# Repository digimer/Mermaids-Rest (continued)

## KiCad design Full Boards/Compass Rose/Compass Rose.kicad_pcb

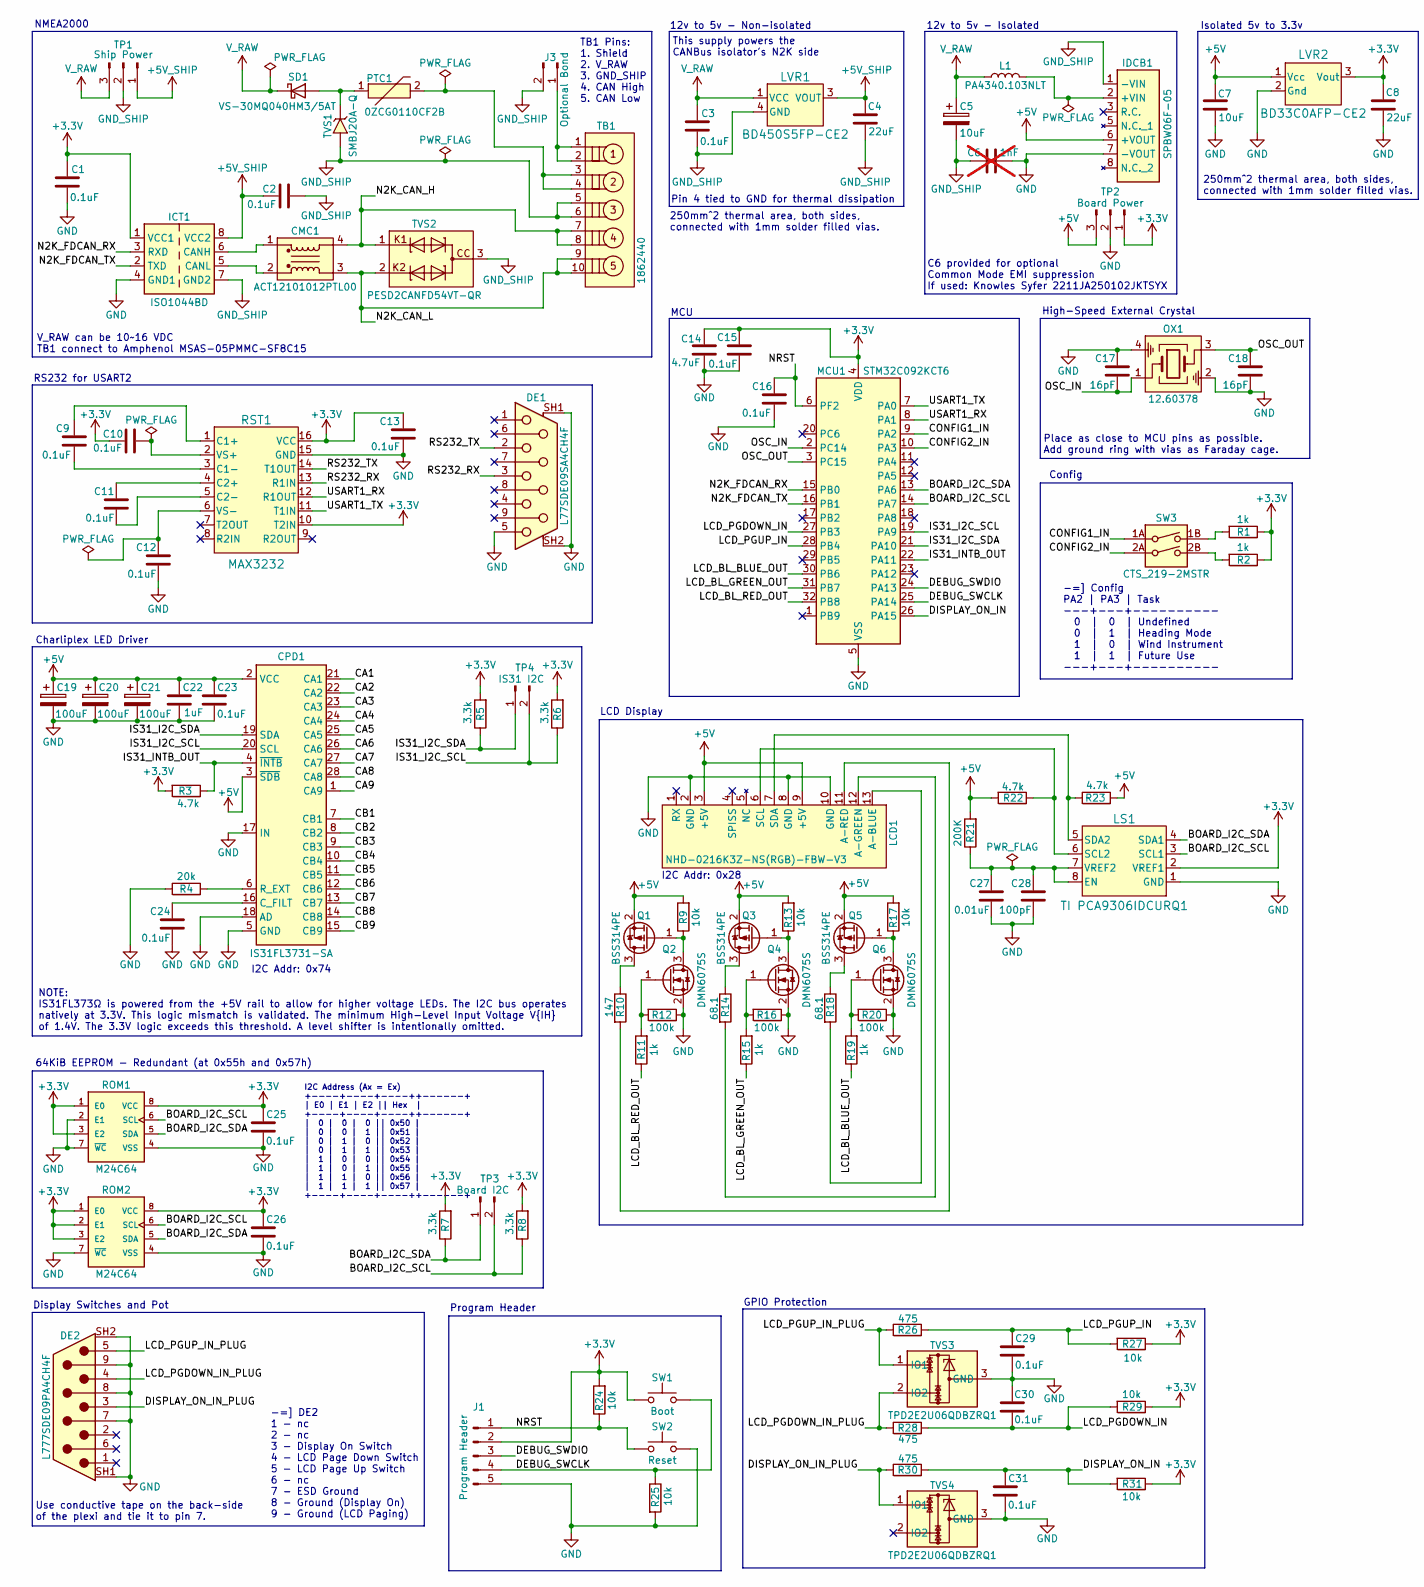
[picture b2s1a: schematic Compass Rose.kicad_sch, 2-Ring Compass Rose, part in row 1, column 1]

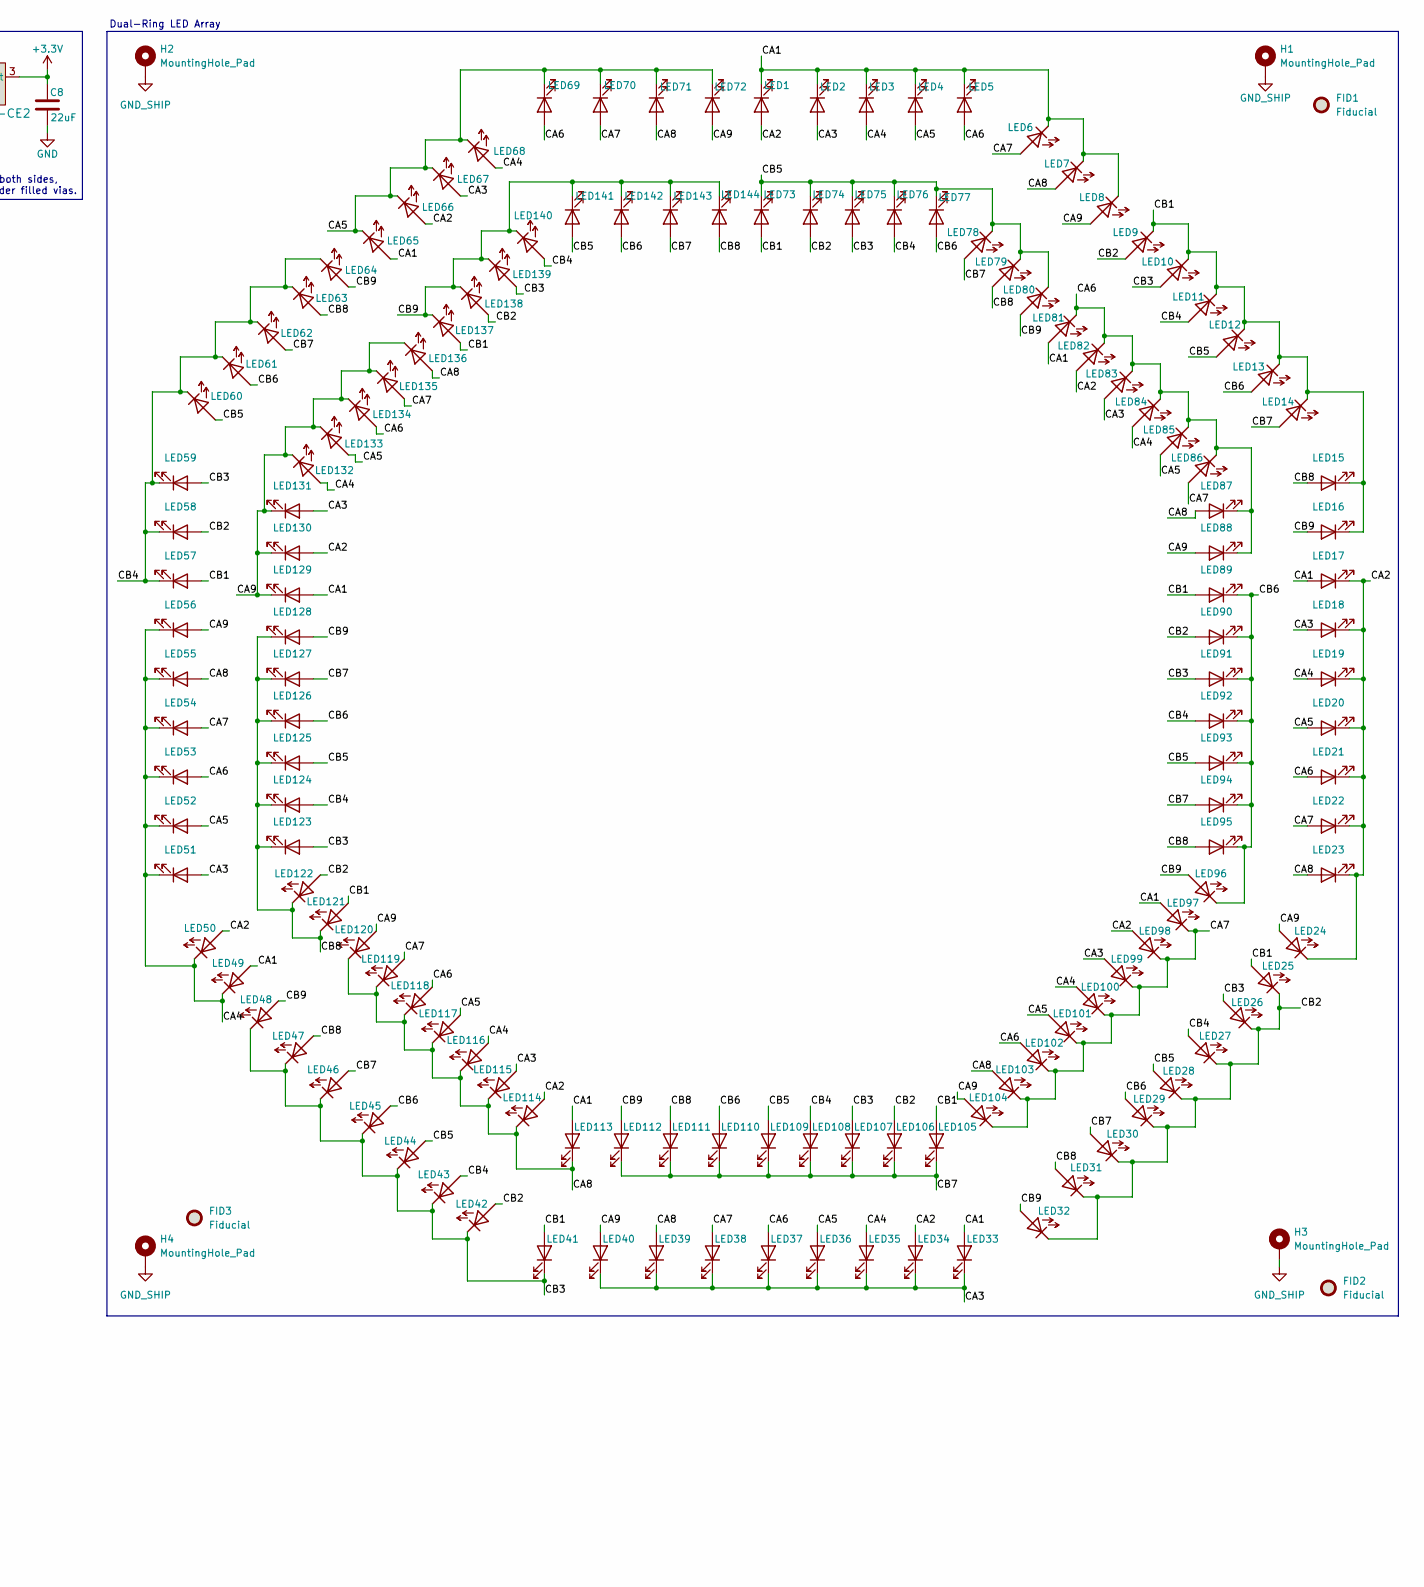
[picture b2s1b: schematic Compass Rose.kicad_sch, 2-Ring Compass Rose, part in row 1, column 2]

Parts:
C1, C2, C3, C9, C10, C11, C12, C13, C15, C16, C23, C24, C25, C26, C29, C30, C31: 0.1uF; Kyocera AVX 0805; Part Kyocera 08051C104K4Z2A
C4, C8: 22uF; Murata GCJ31CR71A; Part Murata GCJ31CR71A226KE01L
C5: 10uF; Kyocera AVX 1206; Part Kyocera 12105C106K4Z2A
C6: 1nF; Knowles Syfer 2211JA25; not fitted
C7: 10uF; TDK CGA5; Part TDK CGA5L1X7R1E106K160DC
C14: 4.7uF; Kyocera AVX 1206; Part Kyocera 12065C475K4Z2A
C17, C18: 16pF; Kemet C0603X; Part Kemet C0603X160J5GACAUTO
C19, C20, C21: 100uF; CP_Radial_D8.0mm_P3.50mm; Part Kemet A7C0KS107M1HAAS031
C22: 1uF; Kemet C1206C; Part Kemet C1206X105J1RACAUTO
C27: 0.01uF; Kemet C0805X; Part Kemet FA18NP01H103JNU06
C28: 100pF; Kemet C0805X; Part Kemet C0805X101J5GACAUTO
CMC1: ACT12101012PTL00; TDK ACT12101012PTL00; Part TDK ACT12101012PTL00
CPD1: IS31FL3731-SA; SSOP-28_5.3x10.2mm_P0.65mm; Part Lumissil IS31FL3731-SALS2-TR
DE1: L77SDE09SA4CH4F; Amphenol_L77SDE09SA4CH4F; Part Amphenol L77SDE09SA4CH4F
DE2: L777SDE09PA4CH4F; Amphenol L777SDE09PA4CH4F; Part AAmphenol L777SDE09PA4CH4F
FID1, FID2, FID3: Fiducial; Fiducial_0.5mm_Mask1.5mm
H1, H2, H3, H4: MountingHole_Pad; MountingHole_4mm_Pad_Via
ICT1: ISO1044BD; TI ISO1044BDR; Part TI ISO1044BDR
IDCB1: SPBW06F-05; Meanwell SPBW06F05; Part Meanwell SPBW06F-05
J1: Program Header; PinHeader_1x05_P2.54mm_Horizontal
J3: Optional Bond; PinHeader_1x02_P2.54mm_Vertical
L1: PA4340.103NLT; Pulse PA4340.103NLT; Part Pulse PA4340.103NLT
LCD1: NHD-0216K3Z-NS(RGB)-FBW-V3; Newhaven Display NHD-0216K3Z-NS(RGB)-FBW-V3; Part Newhaven Display NHD-0216K3Z-NS(RGB)-FB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
LED1, LED2, LED3, LED4, LED5, LED6, LED7, LED8, LED9, LED10, LED11, LED12, LED13, LED14, LED15, LED16, LED17, LED18, LED19, LED20, LED21, LED22, LED23, LED24, LED25, LED26, LED27, LED28, LED29, LED30, LED31, LED32, LED33, LED34, LED35, LED36, LED37, LED38, LED39, LED40, LED41, LED42, LED43, LED44, LED45, LED46, LED47, LED48, LED49, LED50, LED51, LED52, LED53, LED54, LED55, LED56, LED57, LED58, LED59, LED60, LED61, LED62, LED63, LED64, LED65, LED66, LED67, LED68, LED69, LED70, LED71, LED72, LED73, LED74, LED75, LED76, LED77, LED78, LED79, LED80, LED81, LED82, LED83, LED84, LED85, LED86, LED87, LED88, LED89, LED90, LED91, LED92, LED93, LED94, LED95, LED96, LED97, LED98, LED99, LED100, LED101, LED102, LED103, LED104, LED105, LED106, LED107, LED108, LED109, LED110, LED111, LED112, LED113, LED114, LED115, LED116, LED117, LED118, LED119, LED120, LED121, LED122, LED123, LED124, LED125, LED126, LED127, LED128, LED129, LED130, LED131, LED132, LED133, LED134, LED135, LED136, LED137, LED138, LED139, LED140, LED141, LED142, LED143, LED144: WP383SURDTK; Kingbright WP383SURDTK; Part Kingbright WP383SURDTK
LS1: TI PCA9306IDCURQ1; TI PCA9306; Part Texas Instruments PCA9306IDCURQ1
LVR1: BD450S5FP-CE2; Rohm BD4xxS5 TO252-3; Part Rohm BD450S5FP-CE2
LVR2: BD33C0AFP-CE2; Rohm BD33C0; Part Rohm BD33C0AFP-CE2
MCU1: STM32C092KCT6; STM STM32C0 LQFP-32; Part STM STM32C092KCT6
OX1: 12.60378; Crystal_SMD_3225-4Pin_3.2x2.5mm; Part Geyer 12.60378
PTC1: 0ZCG0110CF2B; Bel Fuse 0ZCG; Part Bel Fuse 0ZCG0110CF2B
Q1, Q3, Q5: BSS314PE; SOT-23; Part Infineon BSS314PEH6327XTSA1
Q2, Q4, Q6: DMN6075S; SOT-23; Part Diodes Inc DMN6075SQ-7
R1, R2, R11, R15, R19: 1k; Stackpole RNCP0805; Part Stackpole RNCP0805FTD1K00
R3, R22, R23: 4.7k; Stackpole RMCA0805; Part Stackpole RMCA0805FT4K70-HP
R4: 20k; Stackpole RMCA0805; Part Stackpole RMCA0805FT20K0-HP
R5, R6, R7, R8: 3.3k; Stackpole RNCF0805; Part Stackpole RNCF0805DTE3K30
R9, R13, R17, R24, R25, R27, R29, R31: 10k; Stackpole RMCA0805; Part Stackpole RMCA0805FT10K0-HP
R10: 147; Stackpole RNCP0805; Part Stackpole RNCP0805FTD150R
R12, R16, R20: 100k; Stackpole RMCA0805; Part Stackpole RMCA0805FT100K-HP
R14, R18: 68.1; Stackpole RNCP0805; Part Stackpole RNCP0805FTD68R1
R21: 200K; Yageo AE0805; Part Yageo RNCP0805FTD475R
R26, R28, R30: 475; Stackpole RNCP0805; Part Stackpole RNCP0805FTD475R
ROM1, ROM2: M24C64; STM M24C64-RMN6P; Part STM M24C64-RMN6P
RST1: MAX3232; TI MAX3232EIPWRQ1; Part TI MAX3232EIPWRQ1
SD1: VS-30MQ040HM3/5AT; D_SMA; Part Vishay VS-30MQ040HM3/5AT
SW1: Boot; Same Sky TS03-66; Part Same Sky TS03-66-50-BK-160-LCR-D-67
SW2: Reset; Same Sky TS03-66; Part Same Sky TS03-66-50-BK-160-LCR-D-67
SW3: CTS_219-2MSTR; CTS 219-2MSTR; Part CTS 219-2MSTR
TB1: 1862440; Phoenix Contact 1862440; Part Phoenix Contact 1862440
TP1: Ship Power; PinHeader_1x03_P2.54mm_Vertical
TP2: Board Power; PinHeader_1x03_P2.54mm_Vertical
TP3: Board I2C; PinHeader_1x02_P2.54mm_Vertical
TP4: IS31 I2C; PinHeader_1x02_P2.54mm_Vertical
TVS1: SMBJ20A-Q; Bourns SMBJ20; Part Bourns SMBJ20A-Q
TVS2: PESD2CANFD54VT-QR; Nexperia PESD2CANFD; Part Nexperia PESD2CANFD54VT-QR
TVS3, TVS4: TPD2E2U06QDBZRQ1; TI TPD2E2U06; Part TI TPD2E2U06QDBZRQ1

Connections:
+3.3V: C1.2, C8.2, C10.2, C13.2, C14.1, C15.2, C25.2, C26.2, ICT1.1 (VCC1), J1.2, LS1.2 (VREF1), LVR2.3 (Vout), MCU1.4 (VDD), R1.1, R2.1, R3.2, R5.2, R6.2, R7.2, R8.2, R24.2, R27.1, R29.1, R31.1, ROM1.1 (E0), ROM1.3 (E2), ROM1.8 (VCC), ROM2.1 (E0), ROM2.2 (E1), ROM2.3 (E2), ROM2.8 (VCC), RST1.10 (T2IN), RST1.16 (VCC), SW1.1 (A), SW1.2 (A), TP2.1
+5V: C7.2, C19.1, C20.1, C21.1, C22.1, C23.2, CPD1.2 (VCC), CPD1.3 (~SDB), IDCB1.6 (+VOUT), LCD1.3 (+5V), LCD1.9 (+5V), LVR2.1 (Vcc), Q1.2 (S), Q3.2 (S), Q5.2 (S), R9.2, R13.2, R17.2, R21.2, R22.2, R23.2, TP2.3
+5V_SHIP: C2.2, C4.2, ICT1.8 (VCC2), LVR1.3 (VOUT), TP1.1
/BOARD_I2C_SCL: LS1.3 (SCL1), MCU1.14 (PA7), R8.1, ROM1.6 (SCL), ROM2.6 (SCL), TP3.2
/BOARD_I2C_SDA: LS1.4 (SDA1), MCU1.13 (PA6), R7.1, ROM1.5 (SDA), ROM2.5 (SDA), TP3.1
/CA1: CPD1.21 (CA1), LED1.1 (K), LED2.1 (K), LED3.1 (K), LED4.1 (K), LED5.1 (K), LED6.1 (K), LED7.1 (K), LED8.1 (K), LED17.2 (A), LED33.2 (A), LED49.2 (A), LED65.2 (A), LED81.2 (A), LED97.2 (A), LED113.2 (A), LED129.2 (A)
/CA2: CPD1.22 (CA2), LED1.2 (A), LED17.1 (K), LED18.1 (K), LED19.1 (K), LED20.1 (K), LED21.1 (K), LED22.1 (K), LED23.1 (K), LED24.1 (K), LED34.2 (A), LED50.2 (A), LED66.2 (A), LED82.2 (A), LED98.2 (A), LED114.2 (A), LED130.2 (A)
/CA3: CPD1.23 (CA3), LED2.2 (A), LED18.2 (A), LED33.1 (K), LED34.1 (K), LED35.1 (K), LED36.1 (K), LED37.1 (K), LED38.1 (K), LED39.1 (K), LED40.1 (K), LED51.2 (A), LED67.2 (A), LED83.2 (A), LED99.2 (A), LED115.2 (A), LED131.2 (A)
/CA4: CPD1.24 (CA4), LED3.2 (A), LED19.2 (A), LED35.2 (A), LED49.1 (K), LED50.1 (K), LED51.1 (K), LED52.1 (K), LED53.1 (K), LED54.1 (K), LED55.1 (K), LED56.1 (K), LED68.2 (A), LED84.2 (A), LED100.2 (A), LED116.2 (A), LED132.2 (A)
/CA5: CPD1.25 (CA5), LED4.2 (A), LED20.2 (A), LED36.2 (A), LED52.2 (A), LED65.1 (K), LED66.1 (K), LED67.1 (K), LED68.1 (K), LED69.1 (K), LED70.1 (K), LED71.1 (K), LED72.1 (K), LED85.2 (A), LED101.2 (A), LED117.2 (A), LED133.2 (A)
/CA6: CPD1.26 (CA6), LED5.2 (A), LED21.2 (A), LED37.2 (A), LED53.2 (A), LED69.2 (A), LED81.1 (K), LED82.1 (K), LED83.1 (K), LED84.1 (K), LED85.1 (K), LED86.1 (K), LED87.1 (K), LED88.1 (K), LED102.2 (A), LED118.2 (A), LED134.2 (A)
/CA7: CPD1.27 (CA7), LED6.2 (A), LED22.2 (A), LED38.2 (A), LED54.2 (A), LED70.2 (A), LED86.2 (A), LED97.1 (K), LED98.1 (K), LED99.1 (K), LED100.1 (K), LED101.1 (K), LED102.1 (K), LED103.1 (K), LED104.1 (K), LED119.2 (A), LED135.2 (A)
/CA8: CPD1.28 (CA8), LED7.2 (A), LED23.2 (A), LED39.2 (A), LED55.2 (A), LED71.2 (A), LED87.2 (A), LED103.2 (A), LED113.1 (K), LED114.1 (K), LED115.1 (K), LED116.1 (K), LED117.1 (K), LED118.1 (K), LED119.1 (K), LED120.1 (K), LED136.2 (A)
/CA9: CPD1.1 (CA9), LED8.2 (A), LED24.2 (A), LED40.2 (A), LED56.2 (A), LED72.2 (A), LED88.2 (A), LED104.2 (A), LED120.2 (A), LED129.1 (K), LED130.1 (K), LED131.1 (K), LED132.1 (K), LED133.1 (K), LED134.1 (K), LED135.1 (K), LED136.1 (K)
/CB1: CPD1.7 (CB1), LED9.1 (K), LED10.1 (K), LED11.1 (K), LED12.1 (K), LED13.1 (K), LED14.1 (K), LED15.1 (K), LED16.1 (K), LED25.2 (A), LED41.2 (A), LED57.2 (A), LED73.2 (A), LED89.2 (A), LED105.2 (A), LED121.2 (A), LED137.2 (A)
/CB2: CPD1.8 (CB2), LED9.2 (A), LED25.1 (K), LED26.1 (K), LED27.1 (K), LED28.1 (K), LED29.1 (K), LED30.1 (K), LED31.1 (K), LED32.1 (K), LED42.2 (A), LED58.2 (A), LED74.2 (A), LED90.2 (A), LED106.2 (A), LED122.2 (A), LED138.2 (A)
/CB3: CPD1.9 (CB3), LED10.2 (A), LED26.2 (A), LED41.1 (K), LED42.1 (K), LED43.1 (K), LED44.1 (K), LED45.1 (K), LED46.1 (K), LED47.1 (K), LED48.1 (K), LED59.2 (A), LED75.2 (A), LED91.2 (A), LED107.2 (A), LED123.2 (A), LED139.2 (A)
/CB4: CPD1.10 (CB4), LED11.2 (A), LED27.2 (A), LED43.2 (A), LED57.1 (K), LED58.1 (K), LED59.1 (K), LED60.1 (K), LED61.1 (K), LED62.1 (K), LED63.1 (K), LED64.1 (K), LED76.2 (A), LED92.2 (A), LED108.2 (A), LED124.2 (A), LED140.2 (A)
/CB5: CPD1.11 (CB5), LED12.2 (A), LED28.2 (A), LED44.2 (A), LED60.2 (A), LED73.1 (K), LED74.1 (K), LED75.1 (K), LED76.1 (K), LED77.1 (K), LED78.1 (K), LED79.1 (K), LED80.1 (K), LED93.2 (A), LED109.2 (A), LED125.2 (A), LED141.2 (A)
/CB6: CPD1.12 (CB6), LED13.2 (A), LED29.2 (A), LED45.2 (A), LED61.2 (A), LED77.2 (A), LED89.1 (K), LED90.1 (K), LED91.1 (K), LED92.1 (K), LED93.1 (K), LED94.1 (K), LED95.1 (K), LED96.1 (K), LED110.2 (A), LED126.2 (A), LED142.2 (A)
/CB7: CPD1.13 (CB7), LED14.2 (A), LED30.2 (A), LED46.2 (A), LED62.2 (A), LED78.2 (A), LED94.2 (A), LED105.1 (K), LED106.1 (K), LED107.1 (K), LED108.1 (K), LED109.1 (K), LED110.1 (K), LED111.1 (K), LED112.1 (K), LED127.2 (A), LED143.2 (A)
/CB8: CPD1.14 (CB8), LED15.2 (A), LED31.2 (A), LED47.2 (A), LED63.2 (A), LED79.2 (A), LED95.2 (A), LED111.2 (A), LED121.1 (K), LED122.1 (K), LED123.1 (K), LED124.1 (K), LED125.1 (K), LED126.1 (K), LED127.1 (K), LED128.1 (K), LED144.2 (A)
/CB9: CPD1.15 (CB9), LED16.2 (A), LED32.2 (A), LED48.2 (A), LED64.2 (A), LED80.2 (A), LED96.2 (A), LED112.2 (A), LED128.2 (A), LED137.1 (K), LED138.1 (K), LED139.1 (K), LED140.1 (K), LED141.1 (K), LED142.1 (K), LED143.1 (K), LED144.1 (K)
/CONFIG1_IN: MCU1.9 (PA2), SW3.1A
/CONFIG2_IN: MCU1.10 (PA3), SW3.2A
/DEBUG_SWCLK: J1.4, MCU1.25 (PA14), R25.1, SW1.3 (B), SW1.4 (B)
/DEBUG_SWDIO: J1.3, MCU1.24 (PA13)
/DISPLAY_ON_IN: C31.2, MCU1.26 (PA15), R30.2, R31.2
/DISPLAY_ON_IN_PLUG: DE2.3, R30.1, TVS4.1 (IO1)
/IS31_I2C_SCL: CPD1.20 (SCL), MCU1.19 (PA9), R6.1, TP4.2
/IS31_I2C_SDA: CPD1.19 (SDA), MCU1.21 (PA10), R5.1, TP4.1
/IS31_INTB_OUT: CPD1.4 (~INTB), MCU1.22 (PA11), R3.1
/LCD_BL_BLUE_OUT: MCU1.30 (PB6), R19.1
/LCD_BL_GREEN_OUT: MCU1.31 (PB7), R15.1
/LCD_BL_RED_OUT: MCU1.32 (PB8), R11.1
/LCD_PGDOWN_IN: C30.2, MCU1.27 (PB3), R28.2, R29.2
/LCD_PGDOWN_IN_PLUG: DE2.4, R28.1, TVS3.2 (IO2)
/LCD_PGUP_IN: C29.2, MCU1.28 (PB4), R26.2, R27.2
/LCD_PGUP_IN_PLUG: DE2.5, R26.1, TVS3.1 (IO1)
/N2K_CAN_H: CMC1.4 (O1), TB1.7, TB1.8, TVS2.1
/N2K_CAN_L: CMC1.3 (O2), TB1.9, TB1.10, TVS2.2
/N2K_FDCAN_RX: ICT1.3 (RXD), MCU1.15 (PB0)
/N2K_FDCAN_TX: ICT1.2 (TXD), MCU1.16 (PB1)
/NRST: C16.2, J1.1, MCU1.6 (PF2), R24.1, SW2.1 (A), SW2.2 (A)
/OSC_IN: C17.1, MCU1.2 (PC14), OX1.1
/OSC_OUT: C18.2, MCU1.3 (PC15), OX1.3
/RS232_RX: DE1.3, RST1.13 (R1IN)
/RS232_TX: DE1.2, RST1.14 (T1OUT)
/USART1_RX: MCU1.8 (PA1), RST1.12 (R1OUT)
/USART1_TX: MCU1.7 (PA0), RST1.11 (T1IN)
GND: C1.1, C6.2, C7.1, C8.1, C12.1, C13.1, C14.2, C15.1, C16.1, C17.2, C18.1, C19.2, C20.2, C21.2, C22.2, C23.1, C24.1, C25.1, C26.1, C27.1, C28.1, C29.1, C30.1, C31.1, CPD1.5 (GND), CPD1.17 (IN), CPD1.18 (AD), DE1.5, DE1.SH1, DE1.SH2, DE2.7, DE2.8, DE2.9, DE2.SH1, DE2.SH2, ICT1.4 (GND1), IDCB1.7 (-VOUT), J1.5, LCD1.2 (GND), LCD1.8 (GND), LCD1.10 (GND), LS1.1 (GND), LVR2.2 (Gnd), MCU1.5 (VSS), OX1.2, OX1.4, Q2.2 (S), Q4.2 (S), Q6.2 (S), R4.1, R12.1, R16.1, R20.1, R25.2, ROM1.2 (E1), ROM1.4 (VSS), ROM1.7 (~WC), ROM2.4 (VSS), ROM2.7 (~WC), RST1.15 (GND), SW2.3 (B), SW2.4 (B), TP2.2, TVS3.3 (GND), TVS4.3 (GND)
GND_SHIP: C2.1, C3.1, C4.1, C5.2, C6.1, H1.1 (1_1), H2.1 (1_1), H3.1 (1_1), H4.1 (1_1), ICT1.7 (GND2), IDCB1.1 (-VIN), J3.2, LVR1.4 (GND), TB1.5, TB1.6, TP1.2, TVS1.2 (A), TVS2.3
unnamed: CMC1.1 (I1), ICT1.6 (CANH)
unnamed: CMC1.2 (I2), ICT1.5 (CANL)
unnamed: C24.2, CPD1.16 (C_FILT)
unnamed: CPD1.6 (R_EXT), R4.2
unnamed: IDCB1.2 (+VIN), L1.2
unnamed: J3.1, TB1.1, TB1.2
unnamed: LCD1.13 (A-BLUE), R18.2
unnamed: LCD1.12 (A-GREEN), R14.2
unnamed: LCD1.11 (A-RED), R10.2
unnamed: LCD1.6 (SCL), LS1.6 (SCL2), R22.1
unnamed: LCD1.7 (SDA), LS1.5 (SDA2), R23.1
unnamed: C27.2, C28.2, LS1.7 (VREF2), LS1.8 (EN), R21.1
unnamed: PTC1.2, TB1.3, TB1.4
unnamed: Q1.3 (D), R10.1
unnamed: Q1.1 (G), Q2.3 (D), R9.1
unnamed: Q2.1 (G), R11.2, R12.2
unnamed: Q3.3 (D), R14.1
unnamed: Q3.1 (G), Q4.3 (D), R13.1
unnamed: Q4.1 (G), R15.2, R16.2
unnamed: Q5.3 (D), R18.1
unnamed: Q5.1 (G), Q6.3 (D), R17.1
unnamed: Q6.1 (G), R19.2, R20.2
unnamed: R1.2, SW3.1B
unnamed: R2.2, SW3.2B
unnamed: C9.2, RST1.1 (C1+)
unnamed: C9.1, RST1.3 (C1-)
unnamed: C11.2, RST1.4 (C2+)
unnamed: C11.1, RST1.5 (C2-)
unnamed: C10.1, RST1.2 (VS+)
unnamed: C12.2, RST1.6 (VS-)
unnamed: PTC1.1, SD1.2 (A), TVS1.1 (K)
V_RAW: C3.2, C5.1, L1.1, LVR1.1 (VCC), SD1.1 (K), TP1.3

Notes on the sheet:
Config
I2C Addr: 0x28
RS232 for USART2
High-Speed External Crystal
MCU
TB1 Pins: 1. Shield 2. V_RAW 3. GND_SHIP 4. CAN High 5. CAN Low
Pin 4 tied to GND for thermal dissipation
NMEA2000
LCD Display
Program Header
64KiB EEPROM - Redundant (at 0x55h and 0x57h)
I2C Address (Ax = Ex) +----+----+----++------+ | E0 | E1 | E2 || Hex | +----+----+----++------+ | 0 | 0 | 0 || 0x50 | | 0 | 0 | 1 || 0x51 | | 0 | 1 | 0 || 0x52 | | 0 | 1 | 1 || 0x53 | | 1 | 0 | 0 || 0x54 | | 1 | 0 | 1 || 0x55 | | 1 | 1 | 0 || 0x56 | | 1 | 1 | 1 || 0x57 | +----+----+----++------+
NOTE: IS31FL373Ω is powered from the +5V rail to allow for higher voltage LEDs. The I2C bus operates natively at 3.3V. This logic mismatch is validated. The minimum High-Level Input Voltage V{IH} of 1.4V. The 3.3V logic exceeds this threshold. A level shifter is intentionally omitted.
12v to 5v - Isolated
-=] Config PA2 | PA3 | Task ---+---+---------- 0 | 0 | Undefined 0 | 1 | Heading Mode 1 | 0 | Wind Instrument 1 | 1 | Future Use ---+---+----------
I2C Addr: 0x74
Dual-Ring LED Array
Charliplex LED Driver
Display Switches and Pot
C6 provided for optional Common Mode EMI suppression If used: Knowles Syfer 2211JA250102JKTSYX
12v to 5v - Non-isolated
250mm^2 thermal area, both sides, connected with 1mm solder filled vias.
This supply powers the CANBus isolator's N2K side
Place as close to MCU pins as possible. Add ground ring with vias as Faraday cage.
Use conductive tape on the back-side of the plexi and tie it to pin 7.
V_RAW can be 10~16 VDC TB1 connect to Amphenol MSAS-05PMMC-SF8C15
Isolated 5v to 3.3v
GPIO Protection
-=] DE2 1 - nc 2 - nc 3 - Display On Switch 4 - LCD Page Down Switch 5 - LCD Page Up Switch 6 - nc 7 - ESD Ground 8 - Ground (Display On) 9 - Ground (LCD Paging)

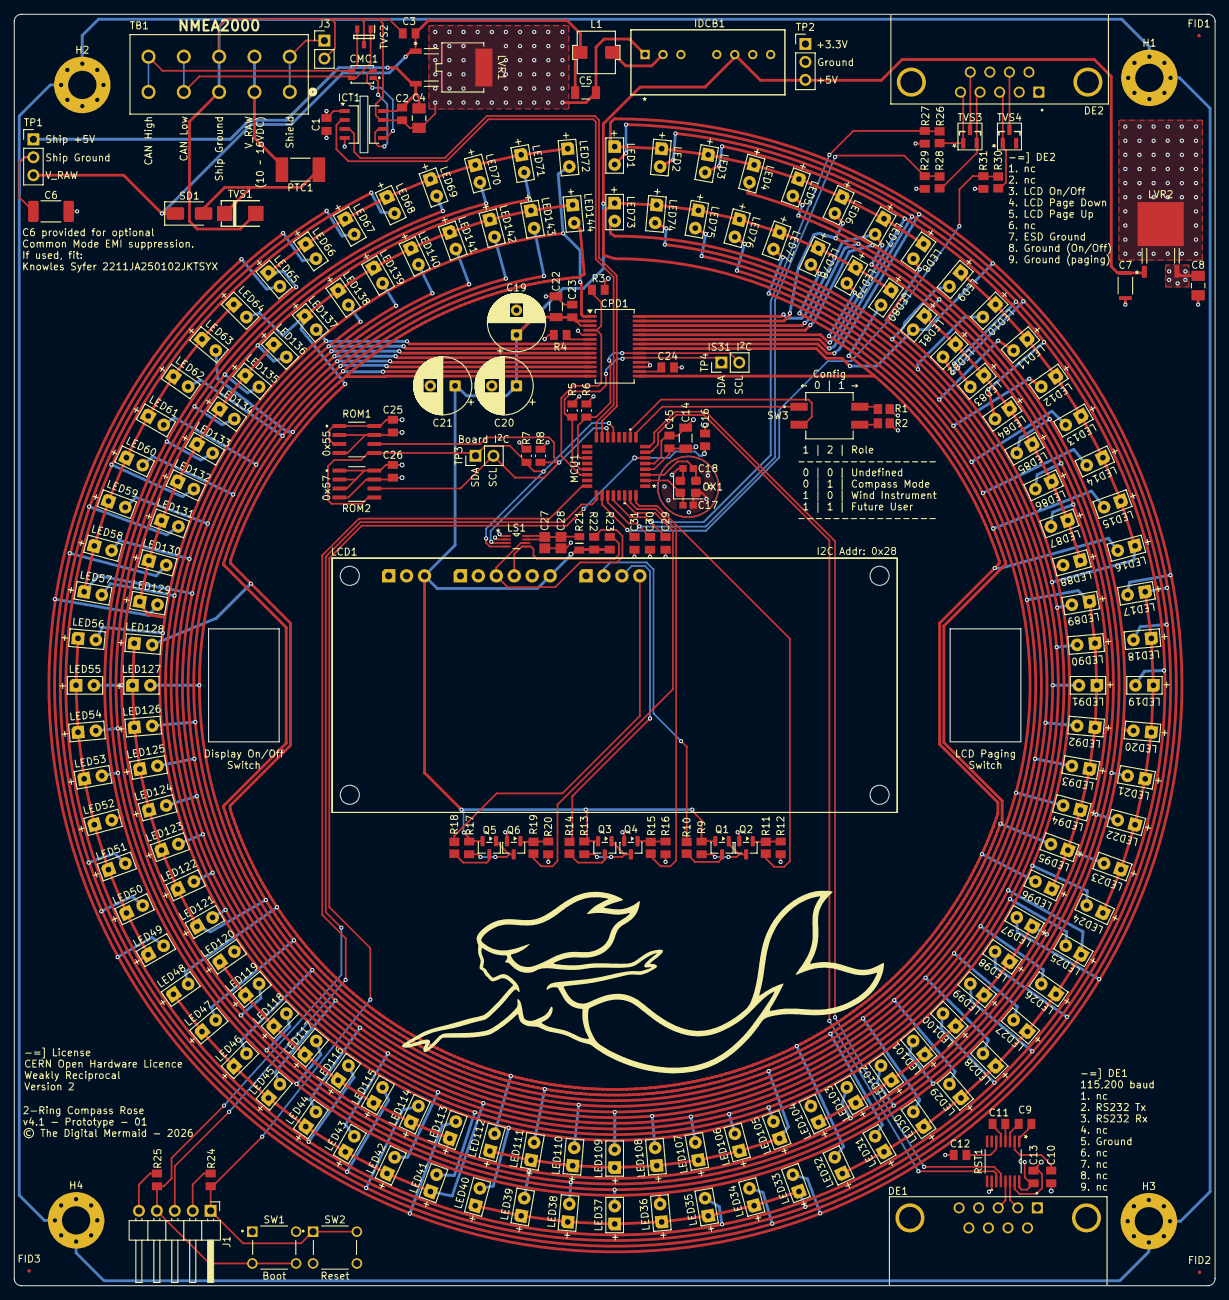
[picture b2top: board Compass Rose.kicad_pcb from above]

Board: 4 copper layers, 170.0 x 180.0 mm, 252 parts (0 on the bottom side), 84 nets.

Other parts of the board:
TDM***: LOGO; Mermaid Silkscreen - 29.9mm

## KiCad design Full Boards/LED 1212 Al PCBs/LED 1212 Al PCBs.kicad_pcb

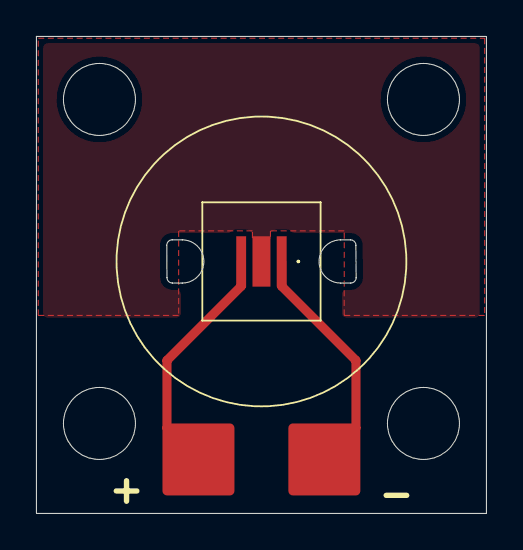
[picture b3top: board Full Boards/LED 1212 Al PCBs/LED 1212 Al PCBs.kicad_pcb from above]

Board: 2 copper layers, 25.0 x 26.5 mm, 3 parts (0 on the bottom side), 2 nets.

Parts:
LED1: LUW CRBP.01-LYMY-G4J4-Y474; Osram LJ CRBP.01
SMD1: - Pad; SolderWirePad_1x01_SMD_4x4mm
SMD2: + Pad; SolderWirePad_1x01_SMD_4x4mm

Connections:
+2V: LED1.2 (A), SMD2.1 (Pin_1_1)
GND: LED1.1 (K), SMD1.1 (Pin_1_1)

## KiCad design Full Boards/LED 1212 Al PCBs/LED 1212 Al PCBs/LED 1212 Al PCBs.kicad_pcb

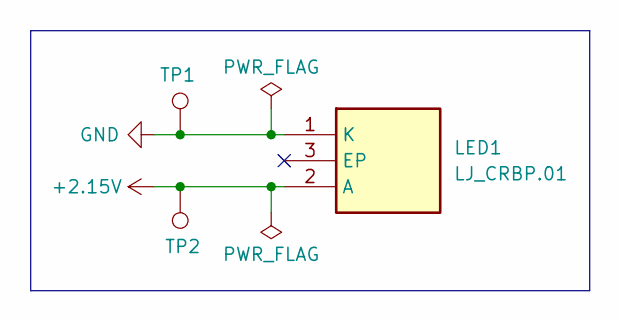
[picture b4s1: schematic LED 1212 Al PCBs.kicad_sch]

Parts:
LED1: LJ_CRBP.01; Osram LJ CRBP.01; Manufacturer_Part_Number LJ CRBP.01-JZLX-27-3A4A; Mouser Part Number 720-LJCRBP01JZA9260
TP1, TP2: TestPoint; TestPoint_Pad_4.0x4.0mm

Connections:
+2.15V: LED1.2 (A), TP2.1 (1_1)
GND: LED1.1 (K), TP1.1 (1_1)

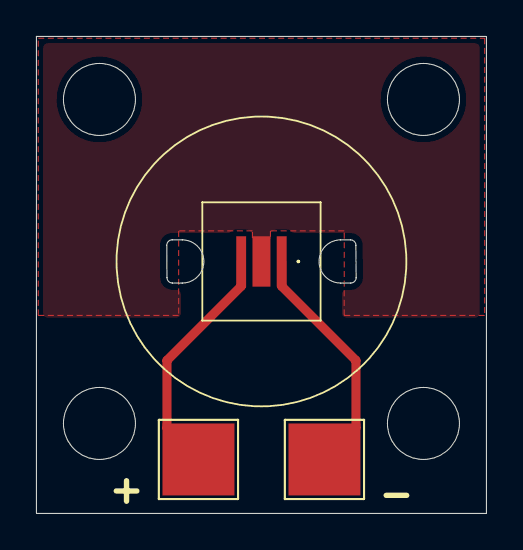
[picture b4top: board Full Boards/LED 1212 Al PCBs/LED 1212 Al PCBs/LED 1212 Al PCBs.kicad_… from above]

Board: 2 copper layers, 25.0 x 26.5 mm, 3 parts (0 on the bottom side), 2 nets.
